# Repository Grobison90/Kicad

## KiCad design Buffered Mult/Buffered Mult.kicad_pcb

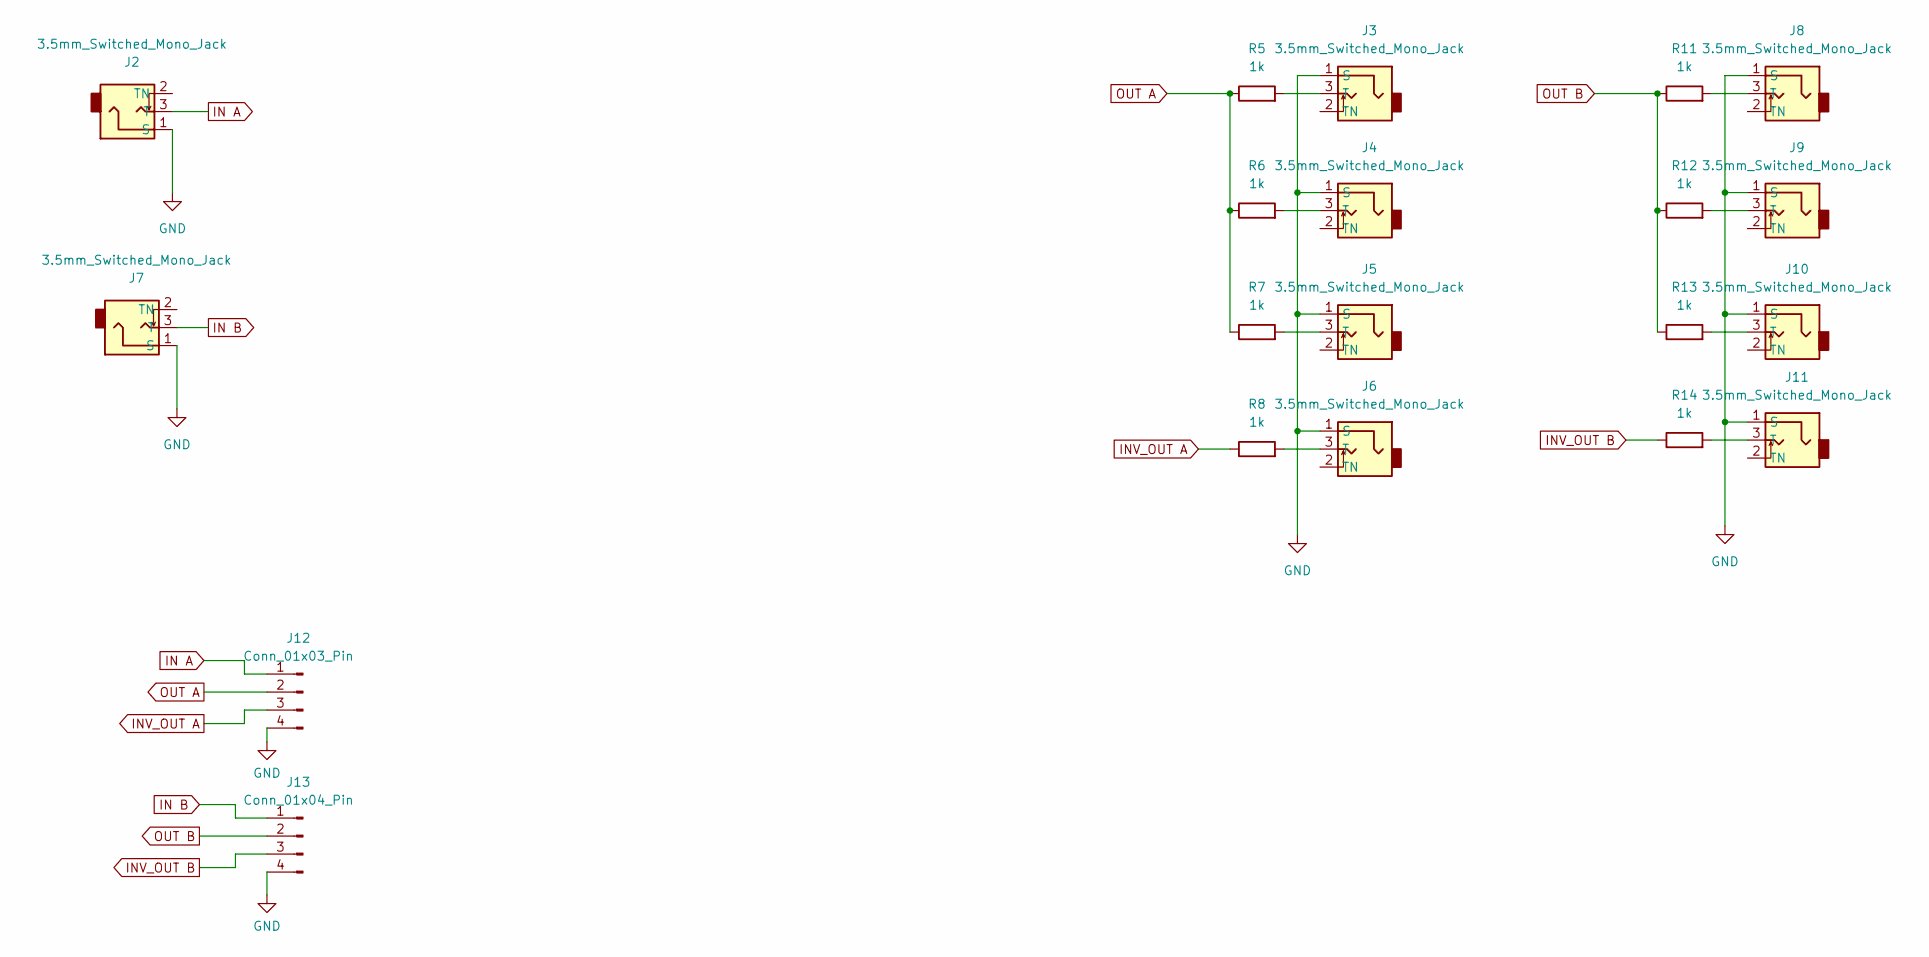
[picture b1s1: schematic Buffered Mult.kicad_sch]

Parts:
J2, J3, J4, J5, J6, J7, J8, J9, J10, J11: 3.5mm_Switched_Mono_Jack; Connector 3.5mm Mono Switched
J12: Conn_01x03_Pin; PinHeader_1x04_P2.54mm_Vertical
J13: Conn_01x04_Pin; PinHeader_1x04_P2.54mm_Vertical
R5, R6, R7, R8, R11, R12, R13, R14: 1k; R_Axial_DIN0411_L9.9mm_D3.6mm_P5.08mm_Vertical

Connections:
GND: J2.1 (S), J3.1 (S), J4.1 (S), J5.1 (S), J6.1 (S), J7.1 (S), J8.1 (S), J9.1 (S), J10.1 (S), J11.1 (S), J12.4, J13.4
IN A: J2.3 (T), J12.1
IN B: J7.3 (T), J13.1
INV_OUT A: J12.3, R8.1
INV_OUT B: J13.3, R14.1
unnamed: J3.3 (T), R5.2
unnamed: J4.3 (T), R6.2
unnamed: J5.3 (T), R7.2
unnamed: J6.3 (T), R8.2
unnamed: J8.3 (T), R11.2
unnamed: J9.3 (T), R12.2
unnamed: J10.3 (T), R13.2
unnamed: J11.3 (T), R14.2
OUT A: J12.2, R5.1, R6.1, R7.1
OUT B: J13.2, R11.1, R12.1, R13.1

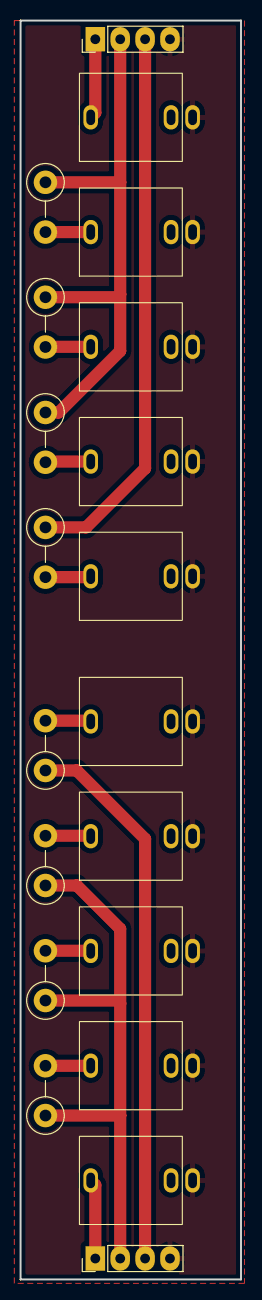
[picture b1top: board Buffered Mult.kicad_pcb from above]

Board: 2 copper layers, 22.5 x 128.5 mm, 20 parts (0 on the bottom side), 15 nets.

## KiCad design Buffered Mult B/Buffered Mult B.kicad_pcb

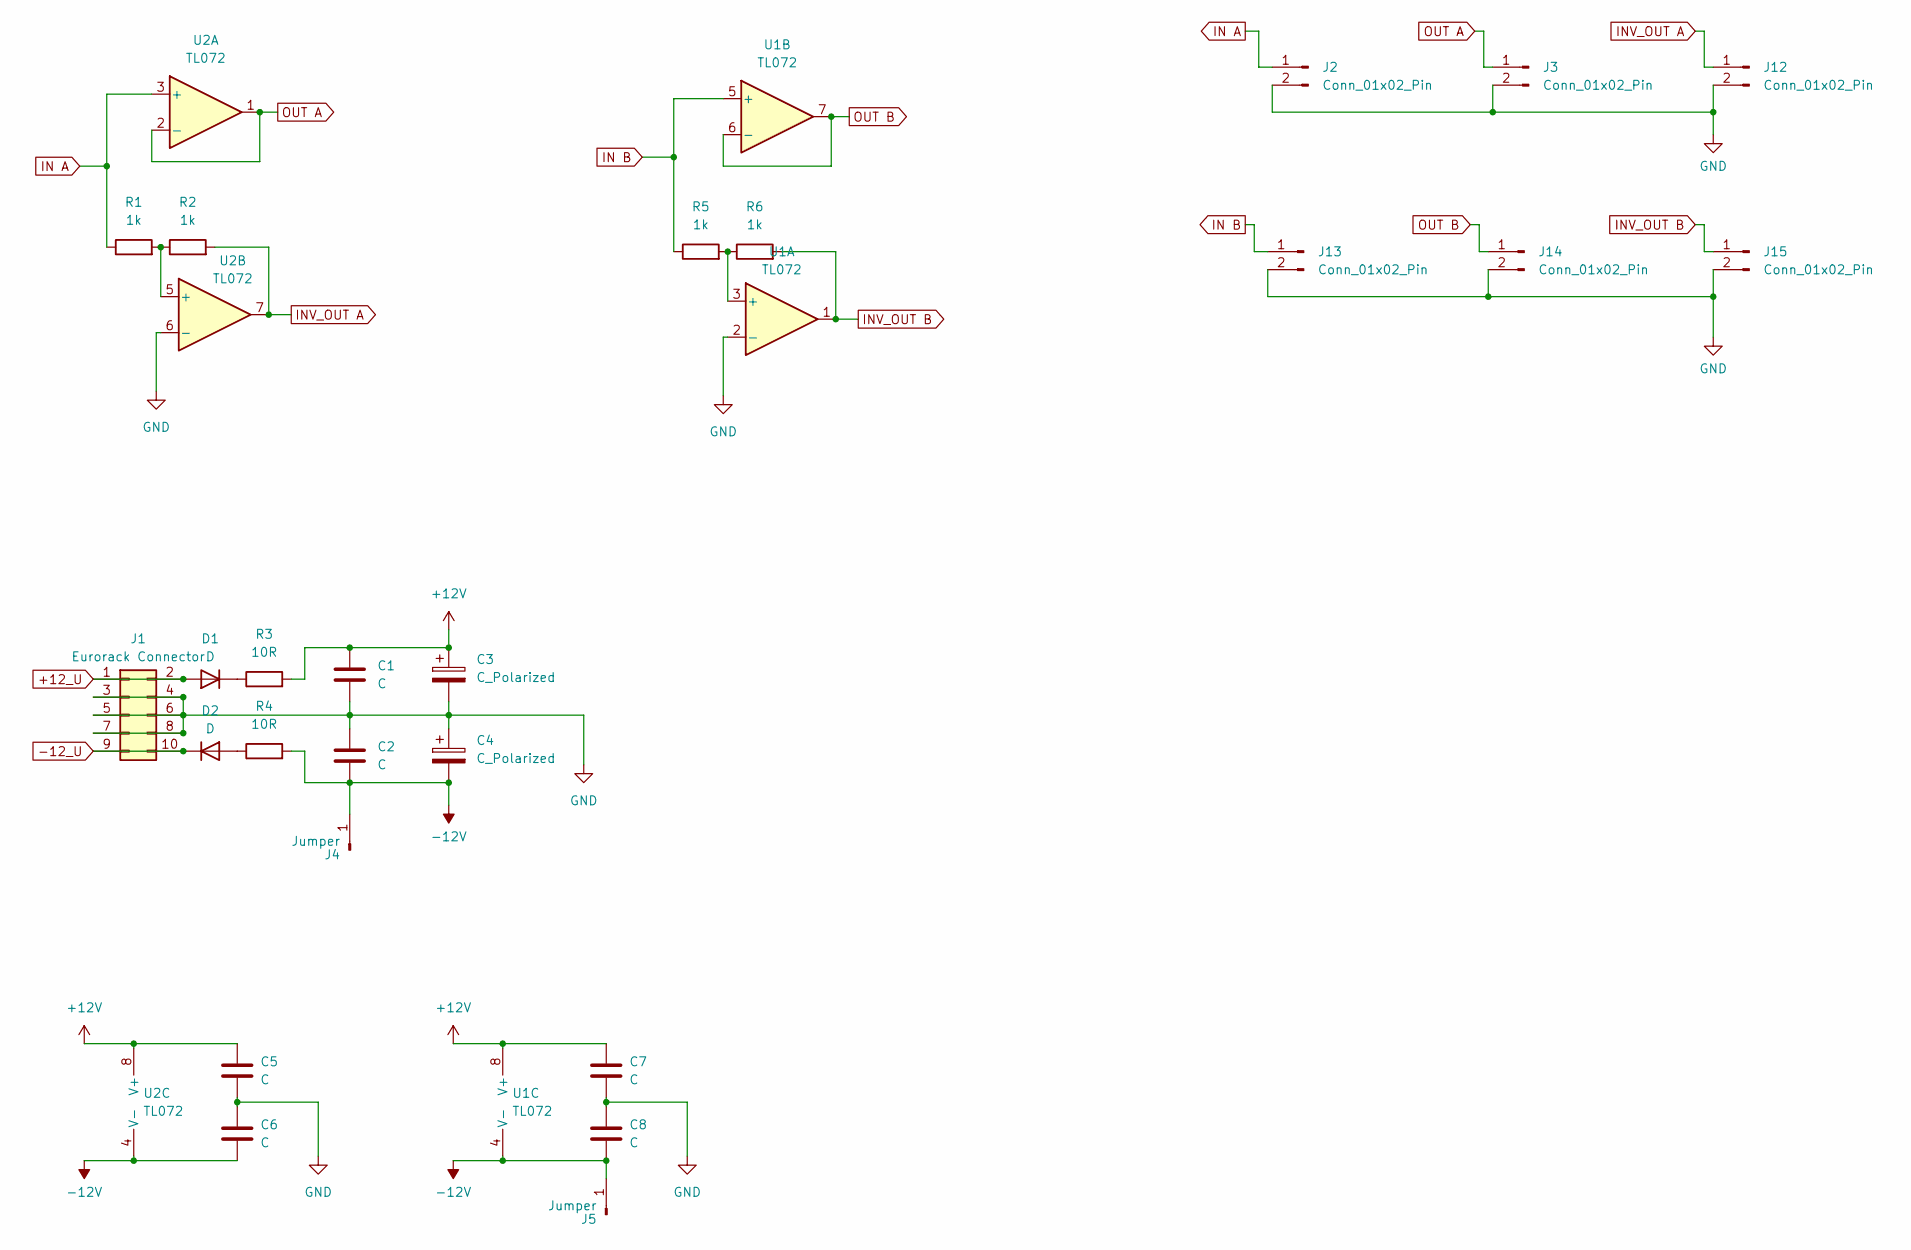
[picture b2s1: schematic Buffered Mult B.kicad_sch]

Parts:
C1, C2: C; C_Disc_D4.7mm_W2.5mm_P5.00mm
C3, C4: C_Polarized; CP_Radial_D5.0mm_P2.50mm
C5, C6, C7, C8: C; C_Disc_D4.3mm_W1.9mm_P5.00mm
D1, D2: D; D_5W_P10.16mm_Horizontal
J1: Eurorack Connector; Eurorack Power (IDC p=2.54)_Stripe_copy
J2, J3, J12, J13, J14, J15: Conn_01x02_Pin; PinHeader_1x02_P2.54mm_Vertical
J4, J5: Jumper; Jumper Wire Hole
R1, R2, R5, R6: 1k; R_Axial_DIN0309_L9.0mm_D3.2mm_P5.08mm_Vertical
R3, R4: 10R; R_Axial_DIN0309_L9.0mm_D3.2mm_P5.08mm_Vertical
U1, U2: TL072; DIP-8_W7.62mm

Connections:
+12V: C1.1, C3.1, C5.1, C7.1, R3.2, U1.8 (V+), U2.8 (V+)
+12_U: D1.2 (A), J1.1, J1.2
-12V: C2.2, C4.2, C6.2, C8.2, J4.1, J5.1, R4.2, U1.4 (V-), U2.4 (V-)
-12_U: D2.1 (K), J1.9, J1.10
GND: C1.2, C2.1, C3.2, C4.1, C5.2, C6.1, C7.2, C8.1, J1.3, J1.4, J1.5, J1.6, J1.7, J1.8, J2.2, J3.2, J12.2, J13.2, J14.2, J15.2, U1.2 (-), U2.6 (-)
IN A: J2.1, R1.1, U2.3 (+)
IN B: J13.1, R5.1, U1.5 (+)
INV_OUT A: J12.1, R2.2, U2.7
INV_OUT B: J15.1, R6.2, U1.1
unnamed: D1.1 (K), R3.1
unnamed: D2.2 (A), R4.1
unnamed: R5.2, R6.1, U1.3 (+)
unnamed: R1.2, R2.1, U2.5 (+)
OUT A: J3.1, U2.1, U2.2 (-)
OUT B: J14.1, U1.6 (-), U1.7

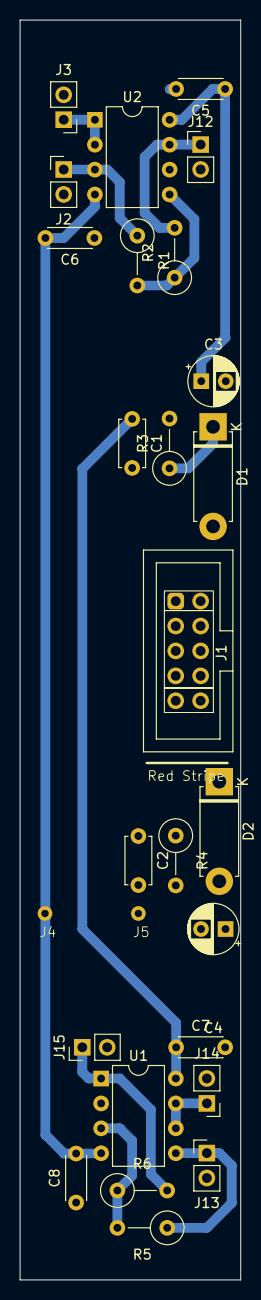
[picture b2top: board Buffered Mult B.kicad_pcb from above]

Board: 2 copper layers, 22.5 x 128.5 mm, 27 parts (0 on the bottom side), 15 nets.

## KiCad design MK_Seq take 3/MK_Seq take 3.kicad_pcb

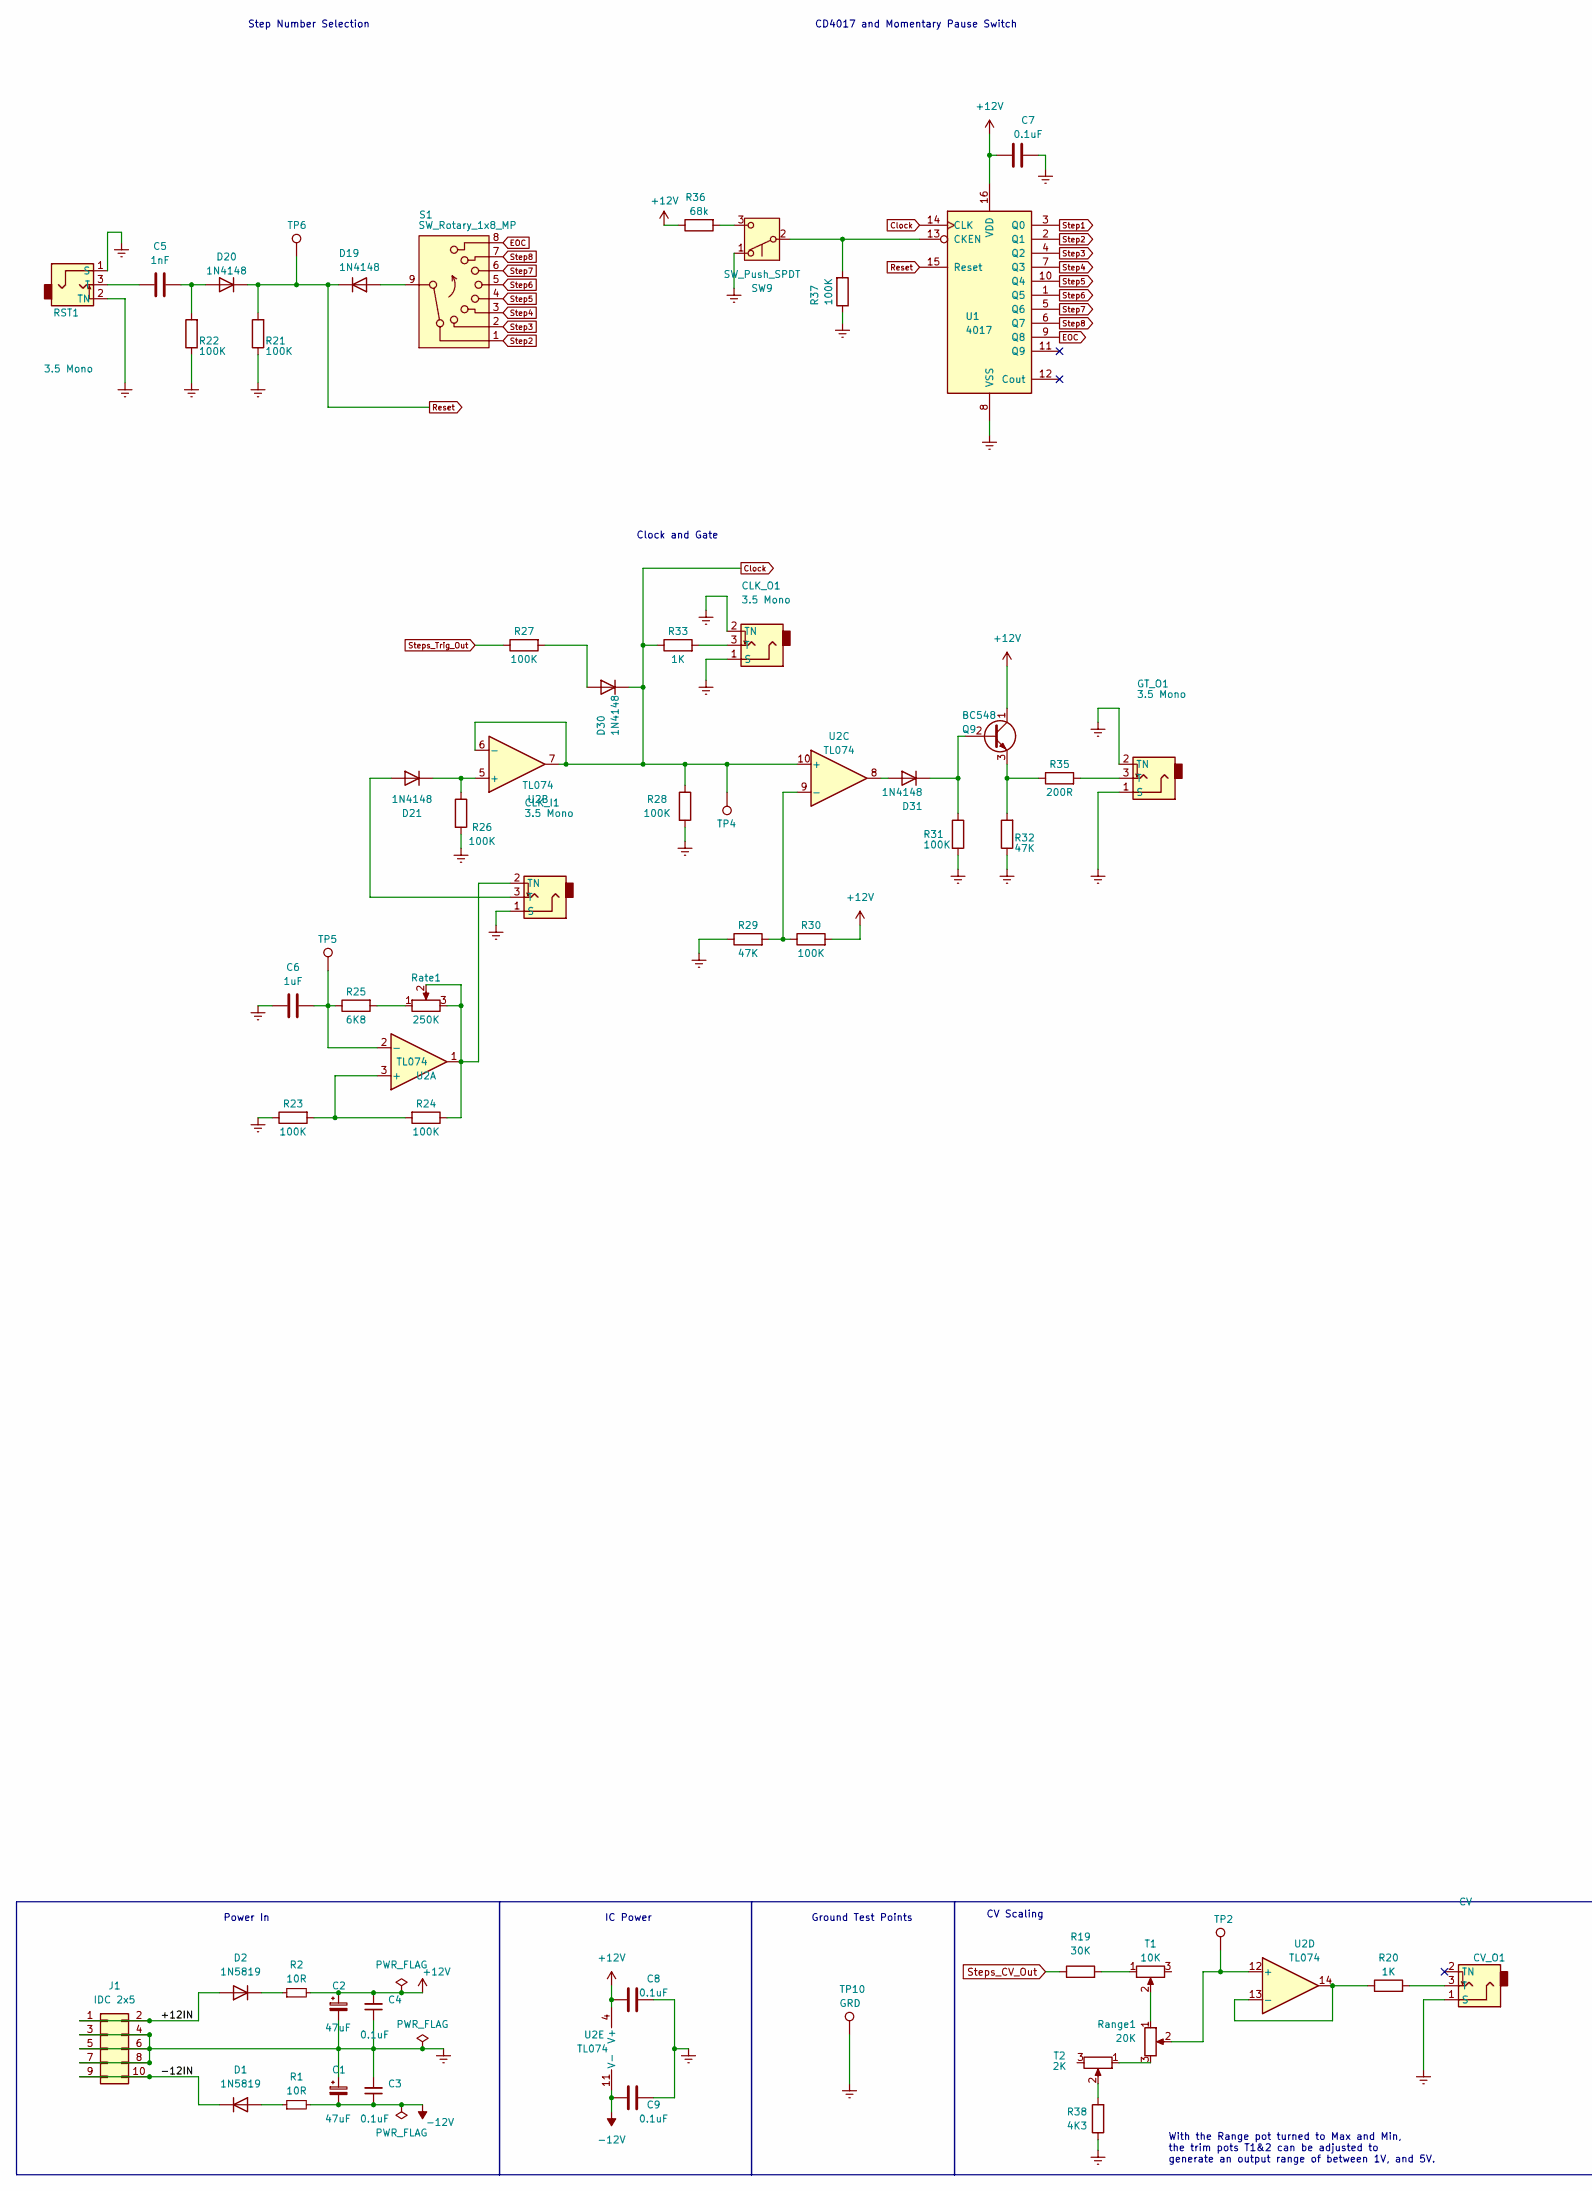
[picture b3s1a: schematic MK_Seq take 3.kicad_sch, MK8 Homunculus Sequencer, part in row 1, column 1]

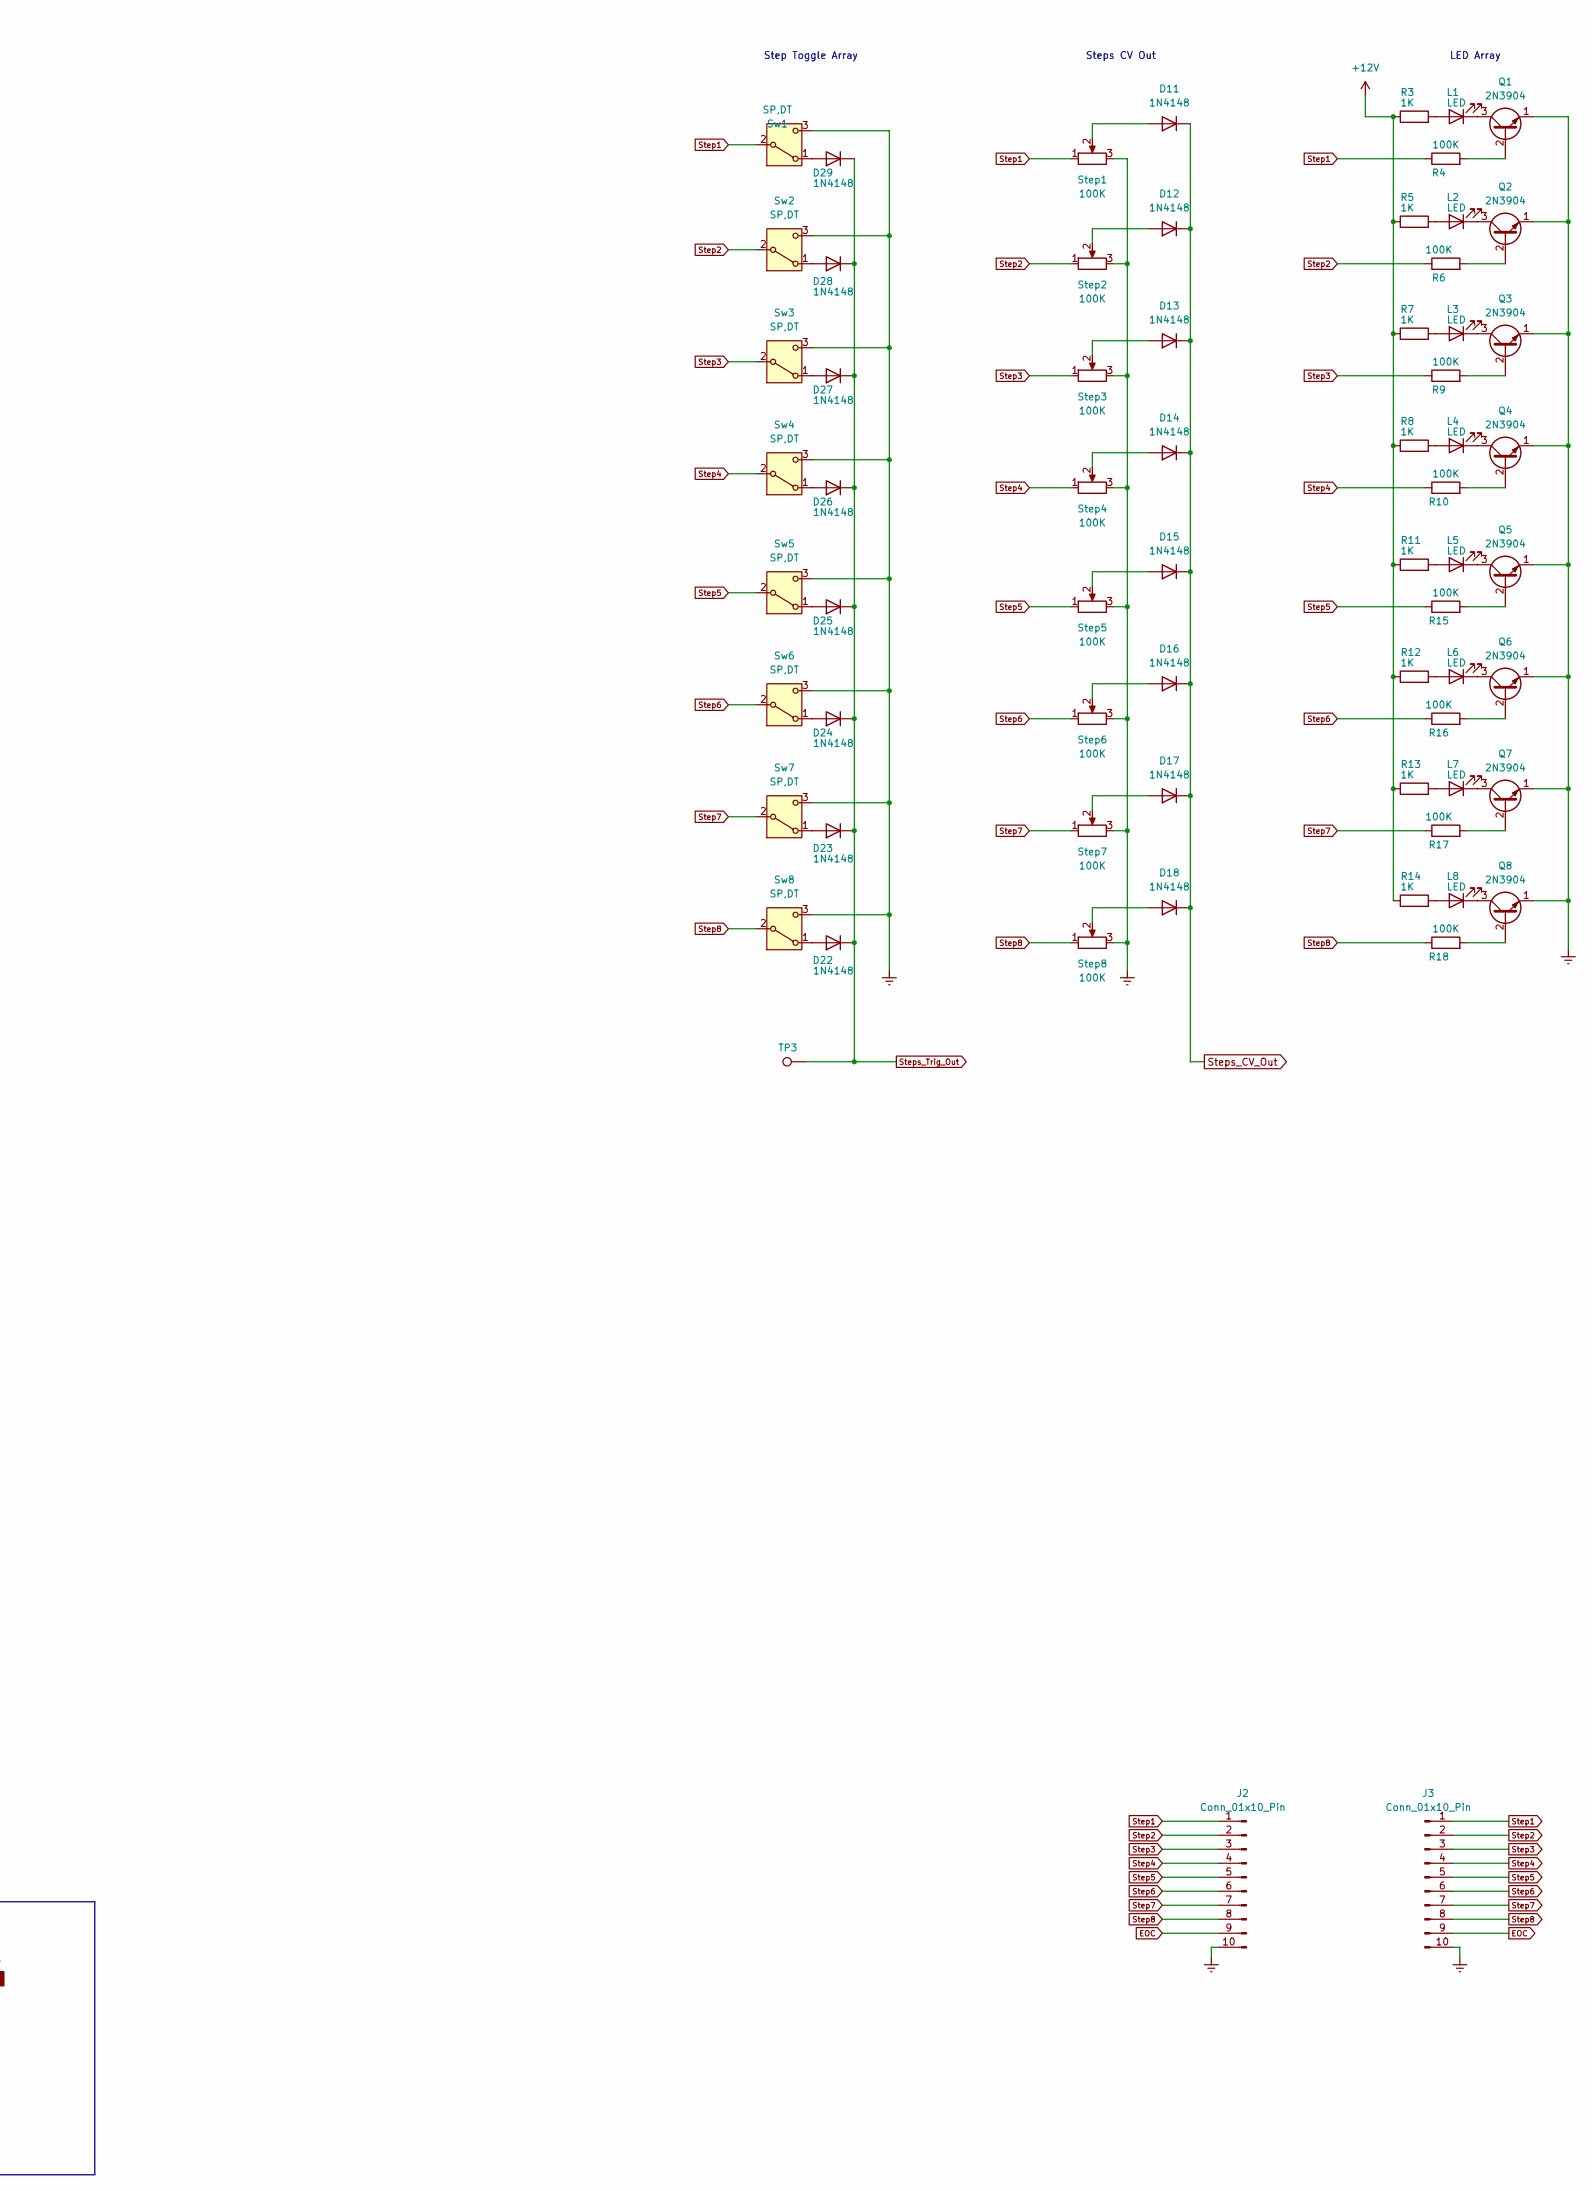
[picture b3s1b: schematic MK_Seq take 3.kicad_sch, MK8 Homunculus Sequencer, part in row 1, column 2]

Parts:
C1, C2: 47uF; CP_Radial_D5.0mm_P2.50mm
C3, C4: 0.1uF; C_Disc_D6.0mm_W2.5mm_P5.00mm
C5: 1nF; C_Disc_D4.3mm_W1.9mm_P5.00mm
C6: 1uF; C_Rect_L7.0mm_W4.5mm_P5.00mm
C7, C8, C9: 0.1uF; C_Disc_D4.7mm_W2.5mm_P5.00mm
CLK_I1: 3.5 Mono; PinSocket_1x03_P1.27mm_Vertical
CLK_O1: 3.5 Mono; PinSocket_1x03_P1.27mm_Vertical
CV_O1: CV; PinSocket_1x03_P1.27mm_Vertical
D1, D2: 1N5819; D_DO-35_SOD27_P7.62mm_Horizontal
D11, D12, D13, D14, D15, D16, D17, D18, D19, D20, D21, D22, D23, D24, D25, D26, D27, D28, D29, D30, D31: 1N4148; D_DO-35_SOD27_P7.62mm_Horizontal
GT_O1: 3.5 Mono; PinSocket_1x03_P1.27mm_Vertical
J1: IDC 2x5; Eurorack Power (IDC p=2.54)_Text
J2: Conn_01x10_Pin; PinHeader_1x10_P2.54mm_Vertical
J3: Conn_01x10_Pin; PinSocket_1x10_P2.54mm_Vertical
L1, L2, L3, L4, L5, L6, L7, L8: LED; LED_D3.0mm
Q1, Q2, Q3, Q4, Q5, Q6, Q7, Q8: 2N3904; TO-92_Inline
Q9: BC548; TO-92_Inline
R1, R2: 10R; R_Axial_DIN0207_L6.3mm_D2.5mm_P2.54mm_Vertical
R3, R5, R7, R8, R11, R12, R13, R14, R20, R33: 1K; R_Axial_DIN0207_L6.3mm_D2.5mm_P2.54mm_Vertical
R4, R6, R9, R10, R15, R16, R17, R18, R21, R22, R23, R24, R26, R27, R28, R30, R31, R37: 100K; R_Axial_DIN0207_L6.3mm_D2.5mm_P2.54mm_Vertical
R19: 30K; R_Axial_DIN0207_L6.3mm_D2.5mm_P15.24mm_Horizontal
R25: 6K8; R_Axial_DIN0207_L6.3mm_D2.5mm_P2.54mm_Vertical
R29, R32: 47K; R_Axial_DIN0207_L6.3mm_D2.5mm_P2.54mm_Vertical
R35: 200R; R_Axial_DIN0207_L6.3mm_D2.5mm_P2.54mm_Vertical
R36: 68k; R_Axial_DIN0207_L6.3mm_D2.5mm_P2.54mm_Vertical
R38: 4K3; R_Axial_DIN0207_L6.3mm_D2.5mm_P2.54mm_Vertical
RST1: 3.5 Mono; PinSocket_1x03_P1.27mm_Vertical
Range1: 20K; PinSocket_1x03_P1.27mm_Vertical
Rate1: 250K; PinSocket_1x03_P1.27mm_Vertical
S1: SW_Rotary_1x8_MP; Rotary Switch, 1 Pole, 8 Positions
SW9: SW_Push_SPDT; SPDT_Momentary
Step1, Step2, Step3, Step4, Step5, Step6, Step7, Step8: 100K; Potentiometer_Alpha_RD901F-40-00D_Single_Vertical
Sw1, Sw2, Sw3, Sw4, Sw5, Sw6, Sw7, Sw8: SP,DT; SPDT ON-ON sw
T1: 10K; PinSocket_1x03_P1.27mm_Vertical
T2: 2K; PinSocket_1x03_P1.27mm_Vertical
TP2: B; TestPoint_Pad_D1.5mm
TP3, TP4: E; TestPoint_Pad_D1.5mm
TP5: D; TestPoint_Pad_D1.5mm
TP6: C; TestPoint_Pad_D1.5mm
TP10: GRD; TestPoint_Bridge_Pitch2.54mm_Drill1.0mm
U1: 4017; DIP-16_W7.62mm
U2: TL074; DIP-14_W7.62mm

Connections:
+12V: C2.1, C4.2, C7.1, C8.1, Q9.1 (C), R2.2, R3.1, R5.1, R7.1, R8.1, R11.1, R12.1, R13.1, R14.1, R30.2, R36.1, U1.16 (VDD), U2.4 (V+)
-12V: C1.2, C3.1, C9.1, R1.2, U2.11 (V-)
/+12IN: D2.2 (A), J1.1, J1.2
/-12IN: D1.1 (K), J1.9, J1.10
Clock: D30.1 (K), R28.1, R33.1, TP4.1, U1.14 (CLK), U2.6 (-), U2.7, U2.10 (+)
EOC: J2.9, J3.9, S1.8, U1.9 (Q8)
Earth: C1.1, C2.2, C3.2, C4.1, C6.1, C7.2, C8.2, C9.2, CLK_I1.1 (S), CLK_O1.1 (S), CLK_O1.2 (TN), CV_O1.1 (S), GT_O1.1 (S), GT_O1.2 (TN), J1.3, J1.4, J1.5, J1.6, J1.7, J1.8, J2.10, J3.10, Q1.1 (E), Q2.1 (E), Q3.1 (E), Q4.1 (E), Q5.1 (E), Q6.1 (E), Q7.1 (E), Q8.1 (E), R21.1, R22.1, R23.1, R26.2, R28.2, R29.1, R31.2, R32.1, R37.1, R38.1, RST1.1 (S), RST1.2 (TN), SW9.1 (A), Step1.3, Step2.3, Step3.3, Step4.3, Step5.3, Step6.3, Step7.3, Step8.3, Sw1.3 (C), Sw2.3 (C), Sw3.3 (C), Sw4.3 (C), Sw5.3 (C), Sw6.3 (C), Sw7.3 (C), Sw8.3 (C), TP10.1, U1.8 (VSS)
unnamed: CLK_I1.3 (T), D21.2 (A)
unnamed: CLK_I1.2 (TN), R24.1, Rate1.2, Rate1.3, U2.1
unnamed: CLK_O1.3 (T), R33.2
unnamed: CV_O1.3 (T), R20.2
unnamed: D1.2 (A), R1.1
unnamed: D2.1 (K), R2.1
unnamed: D11.2 (A), Step1.2
unnamed: D12.2 (A), Step2.2
unnamed: D13.2 (A), Step3.2
unnamed: D14.2 (A), Step4.2
unnamed: D15.2 (A), Step5.2
unnamed: D16.2 (A), Step6.2
unnamed: D17.2 (A), Step7.2
unnamed: D18.2 (A), Step8.2
unnamed: D19.2 (A), S1.9
unnamed: C5.2, D20.2 (A), R22.2
unnamed: D21.1 (K), R26.1, U2.5 (+)
unnamed: D22.2 (A), Sw8.1 (A)
unnamed: D23.2 (A), Sw7.1 (A)
unnamed: D24.2 (A), Sw6.1 (A)
unnamed: D25.2 (A), Sw5.1 (A)
unnamed: D26.2 (A), Sw4.1 (A)
unnamed: D27.2 (A), Sw3.1 (A)
unnamed: D28.2 (A), Sw2.1 (A)
unnamed: D29.2 (A), Sw1.1 (A)
unnamed: D30.2 (A), R27.2
unnamed: D31.2 (A), U2.8
unnamed: D31.1 (K), Q9.2 (B), R31.1
unnamed: GT_O1.3 (T), R35.2
unnamed: L1.2 (A), R3.2
unnamed: L1.1 (K), Q1.3 (C)
unnamed: L2.2 (A), R5.2
unnamed: L2.1 (K), Q2.3 (C)
unnamed: L3.2 (A), R7.2
unnamed: L3.1 (K), Q3.3 (C)
unnamed: L4.2 (A), R8.2
unnamed: L4.1 (K), Q4.3 (C)
unnamed: L5.2 (A), R11.2
unnamed: L5.1 (K), Q5.3 (C)
unnamed: L6.2 (A), R12.2
unnamed: L6.1 (K), Q6.3 (C)
unnamed: L7.2 (A), R13.2
unnamed: L7.1 (K), Q7.3 (C)
unnamed: L8.2 (A), R14.2
unnamed: L8.1 (K), Q8.3 (C)
unnamed: Q1.2 (B), R4.2
unnamed: Q2.2 (B), R6.2
unnamed: Q3.2 (B), R9.2
unnamed: Q4.2 (B), R10.2
unnamed: Q5.2 (B), R15.2
unnamed: Q6.2 (B), R16.2
unnamed: Q7.2 (B), R17.2
unnamed: Q8.2 (B), R18.2
unnamed: Q9.3 (E), R32.2, R35.1
unnamed: R19.2, T1.1
unnamed: R25.2, Rate1.1
unnamed: R38.2, T2.2
unnamed: C5.1, RST1.3 (T)
unnamed: Range1.1, T1.2
unnamed: Range1.3, T2.1
unnamed: R37.2, SW9.2 (B), U1.13 (CKEN)
unnamed: R36.2, SW9.3 (C)
unnamed: R23.2, R24.2, U2.3 (+)
unnamed: C6.2, R25.1, TP5.1, U2.2 (-)
unnamed: R29.2, R30.1, U2.9 (-)
unnamed: Range1.2, TP2.1, U2.12 (+)
unnamed: R20.1, U2.13 (-), U2.14
Reset: D19.1 (K), D20.1 (K), R21.2, TP6.1, U1.15 (Reset)
Step1: J2.1, J3.1, R4.1, Step1.1, Sw1.2 (B), U1.3 (Q0)
Step2: J2.2, J3.2, R6.1, S1.1, Step2.1, Sw2.2 (B), U1.2 (Q1)
Step3: J2.3, J3.3, R9.1, S1.2, Step3.1, Sw3.2 (B), U1.4 (Q2)
Step4: J2.4, J3.4, R10.1, S1.3, Step4.1, Sw4.2 (B), U1.7 (Q3)
Step5: J2.5, J3.5, R15.1, S1.4, Step5.1, Sw5.2 (B), U1.10 (Q4)
Step6: J2.6, J3.6, R16.1, S1.5, Step6.1, Sw6.2 (B), U1.1 (Q5)
Step7: J2.7, J3.7, R17.1, S1.6, Step7.1, Sw7.2 (B), U1.5 (Q6)
Step8: J2.8, J3.8, R18.1, S1.7, Step8.1, Sw8.2 (B), U1.6 (Q7)
Steps_CV_Out: D11.1 (K), D12.1 (K), D13.1 (K), D14.1 (K), D15.1 (K), D16.1 (K), D17.1 (K), D18.1 (K), R19.1
Steps_Trig_Out: D22.1 (K), D23.1 (K), D24.1 (K), D25.1 (K), D26.1 (K), D27.1 (K), D28.1 (K), D29.1 (K), R27.1, TP3.1

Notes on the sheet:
IC Power
Step Toggle Array
CD4017 and Momentary Pause Switch
Steps CV Out
With the Range pot turned to Max and Min, the trim pots T1&2 can be adjusted to generate an output range of between 1V, and 5V.
CV Scaling
Power In
LED Array
Clock and Gate
Ground Test Points
Step Number Selection

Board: 2 copper layers, 124 parts (0 on the bottom side), 85 nets, no tracks yet.

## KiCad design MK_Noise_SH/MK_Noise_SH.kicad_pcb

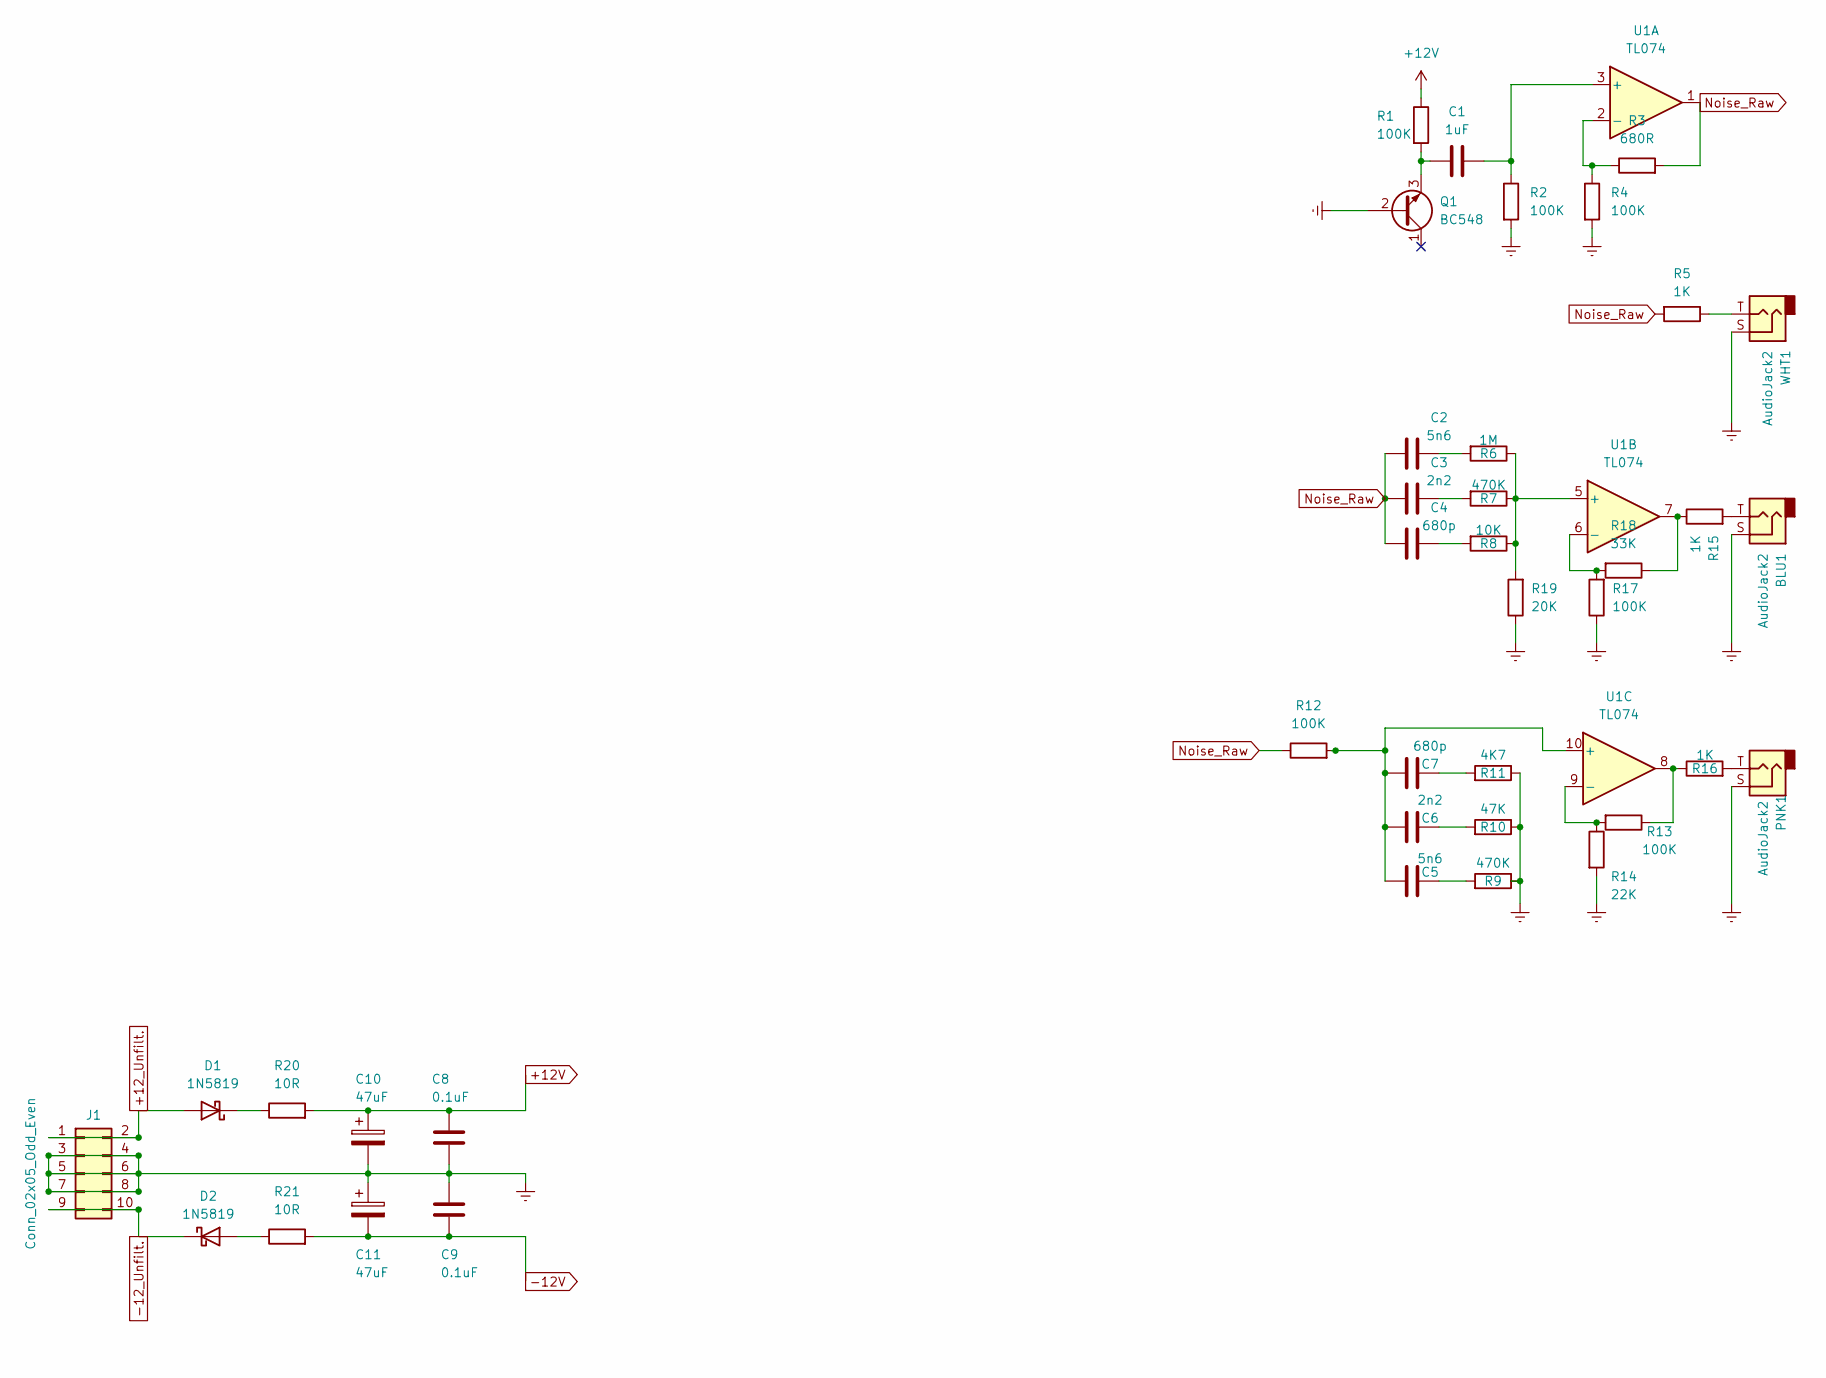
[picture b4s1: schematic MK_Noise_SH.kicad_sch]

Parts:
BLU1: AudioJack2; Jack_3.5mm_CUI_SJ1-3523N_Horizontal
C1: 1uF; C_Disc_D4.3mm_W1.9mm_P5.00mm
C2, C5: 5n6; C_Disc_D4.3mm_W1.9mm_P5.00mm
C3, C6: 2n2; C_Disc_D4.3mm_W1.9mm_P5.00mm
C4, C7: 680p; C_Disc_D4.3mm_W1.9mm_P5.00mm
C8, C9: 0.1uF; C_Disc_D4.3mm_W1.9mm_P5.00mm
C10, C11: 47uF; CP_Radial_D5.0mm_P2.00mm
D1, D2: 1N5819; D_DO-41_SOD81_P2.54mm_Vertical_KathodeUp
J1: Conn_02x05_Odd_Even; PinHeader_2x05_P2.54mm_Horizontal
PNK1: AudioJack2; Jack_3.5mm_CUI_SJ1-3523N_Horizontal
Q1: BC548; TO-92_Inline
R1, R2, R4, R12, R13, R17: 100K; R_0805_2012Metric
R3: 680R; R_0805_2012Metric
R5, R15, R16: 1K; R_0805_2012Metric
R6: 1M; R_0805_2012Metric
R7, R9: 470K; R_0805_2012Metric
R8: 10K; R_0805_2012Metric
R10: 47K; R_0805_2012Metric
R11: 4K7; R_0805_2012Metric
R14: 22K; R_0805_2012Metric
R18: 33K; R_0805_2012Metric
R19: 20K; R_0805_2012Metric
R20, R21: 10R; R_0805_2012Metric
U1: TL074; SOIC-14_3.9x8.7mm_P1.27mm
WHT1: AudioJack2; Jack_3.5mm_CUI_SJ1-3523N_Horizontal

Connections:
+12V: C8.1, C10.1, R1.1, R20.2
+12_Unfilt.: D1.2 (A), J1.1, J1.2
-12V: C9.2, C11.2, R21.2
-12_Unfilt.: D2.1 (K), J1.9, J1.10
Earth: BLU1.S, C8.2, C9.1, C10.2, C11.1, J1.3, J1.4, J1.5, J1.6, J1.7, J1.8, PNK1.S, Q1.2 (B), R2.2, R4.2, R9.1, R10.1, R11.1, R14.2, R17.1, R19.1, WHT1.S
unnamed: BLU1.T, R15.2
unnamed: C2.1, R6.2
unnamed: C3.1, R7.2
unnamed: C4.1, R8.2
unnamed: C5.1, R9.2
unnamed: C6.1, R10.2
unnamed: C7.1, R11.2
unnamed: D1.1 (K), R20.1
unnamed: D2.2 (A), R21.1
unnamed: PNK1.T, R16.2
unnamed: C1.2, Q1.3 (E), R1.2
unnamed: R5.1, WHT1.T
unnamed: R13.1, R16.1, U1.8
unnamed: R15.1, R18.1, U1.7
unnamed: C1.1, R2.1, U1.3 (+)
unnamed: R3.1, R4.1, U1.2 (-)
unnamed: R6.1, R7.1, R8.1, R19.2, U1.5 (+)
unnamed: R17.2, R18.2, U1.6 (-)
unnamed: C5.2, C6.2, C7.2, R12.2, U1.10 (+)
unnamed: R13.2, R14.1, U1.9 (-)
Noise_Raw: C2.2, C3.2, C4.2, R3.2, R5.2, R12.1, U1.1

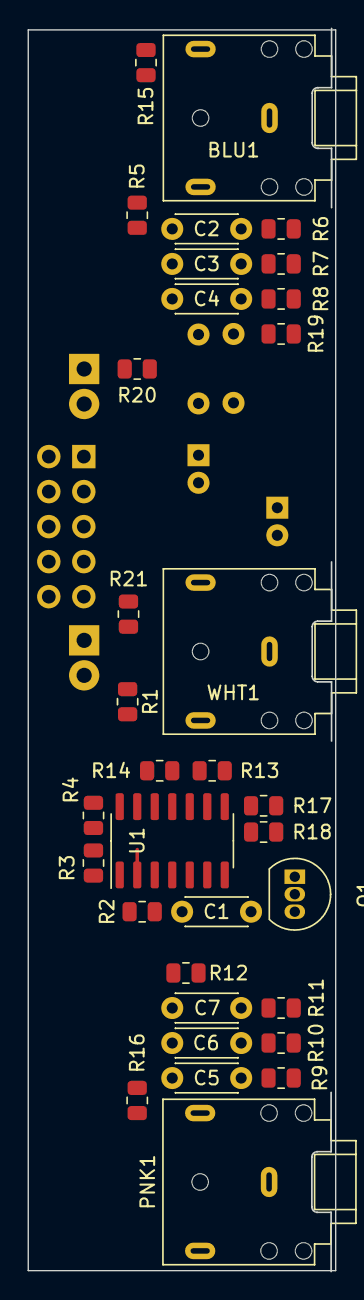
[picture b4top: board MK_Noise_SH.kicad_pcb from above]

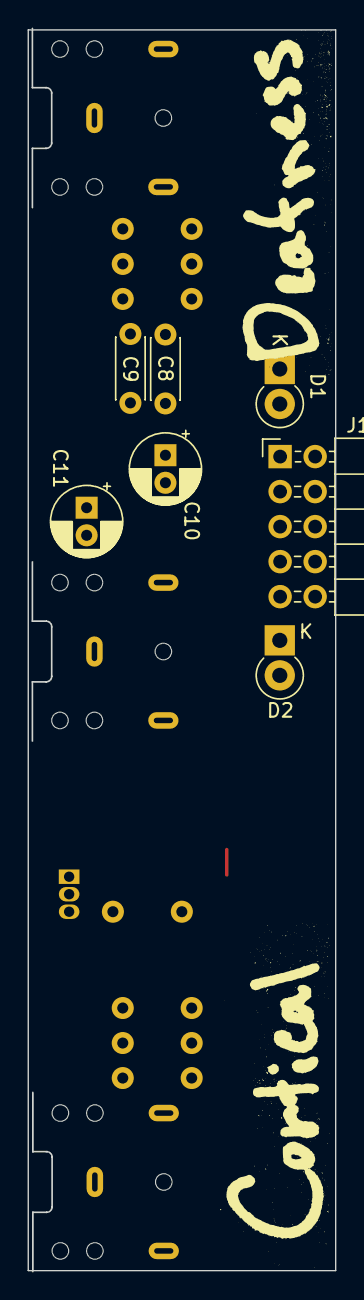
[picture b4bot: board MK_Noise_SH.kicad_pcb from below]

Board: 2 copper layers, 22.3 x 90.2 mm, 40 parts (7 on the bottom side), 26 nets.
